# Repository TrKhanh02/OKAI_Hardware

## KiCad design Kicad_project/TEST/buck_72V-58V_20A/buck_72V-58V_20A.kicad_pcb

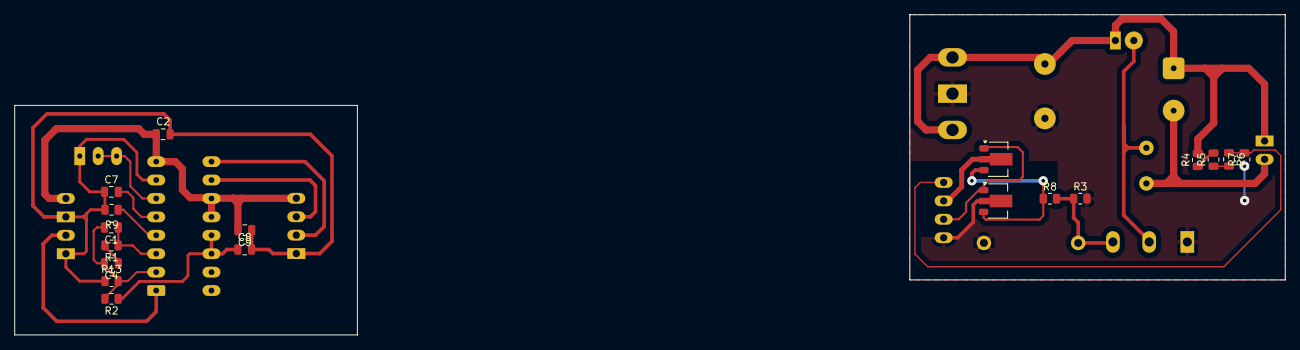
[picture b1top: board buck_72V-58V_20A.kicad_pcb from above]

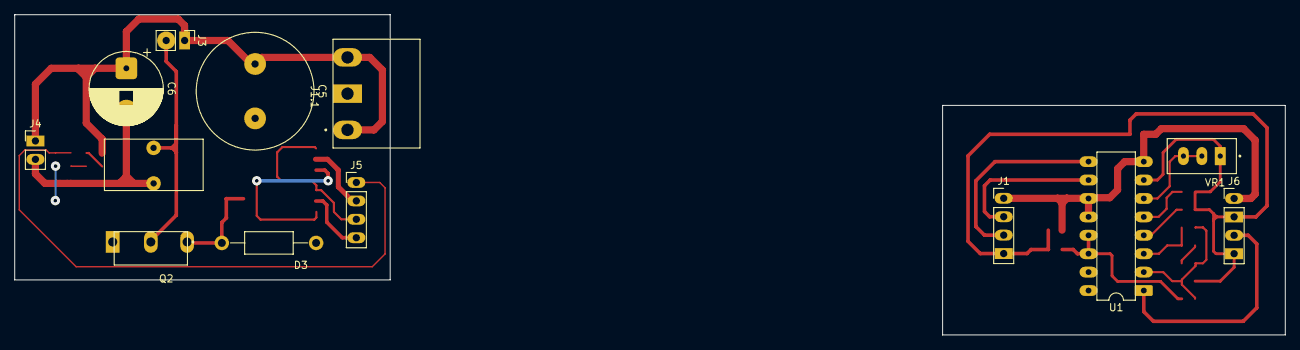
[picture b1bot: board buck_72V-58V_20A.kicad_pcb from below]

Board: 2 copper layers, 175.2 x 44.2 mm, 31 parts (13 on the bottom side), 23 nets.

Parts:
C1: 221; C_0805_2012Metric
C2, C8, C9: 104; C_0805_2012Metric
C4: 103; C_0805_2012Metric
C5: C; C_Radial_D16.0mm_H25.0mm_P7.50mm
C6: C_Polarized; CP_Radial_D10.0mm_P2.50mm
C7: 4.7nF; C_0805_2012Metric
D3: P6KE12CA; DIOAD1300W80L670D310
J1, J5, J6: Conn_01x04_Pin; PinHeader_1x04_P2.54mm_Vertical
J1.1: Nguon IN; CUI_TBP04R1-500-03BE
J3, J4: Conn_01x02_Pin; PinHeader_1x02_P2.54mm_Vertical
L1.1: FIT68-3; IND_FIT68-3
Q1: D882; TO-252
Q2: FDA50N50; TO254P1010X460X1940-3
Q3: B772
R1, R2, R3, R4, R5, R9, R13: 10K; R_0805_2012Metric
R6, R8: 1K; R_0805_2012Metric
R7: 5.6K; R_0805_2012Metric
U1: TL494; DIP-16_W7.62mm
VR1: VR1; TRIM_3296W-1-104LF

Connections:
+12V: C2.2, C9.2, J1.1, J6.1, U1.8 (C1), U1.11 (C2), U1.12 (VCC)
/16V: C5.1, C6.1, J1.1.1, J1.1.3, J3.1, J4.1
/B: C6.2, J4.2, L1.1.2, R4.2
/E: J5.3, Q1.1, Q3.1 (B)
/E1: J1.3, U1.9 (E1)
/E2: J1.2, U1.10 (E2)
/VCC: J5.2, Q1.3
/Vadj: J6.3, U1.1 (1IN+)
/Vadj1: J5.1, R6.1, R7.2
/Vref: C8.1, R2.1, U1.13 (OUTCTRL), U1.14 (REF)
GND: C2.1, C7.1, C8.2, C9.1, J1.4, J6.2, J6.4, R9.2, R13.1, U1.7 (GND), VR1.1
GND1: C5.2, D3.1, J1.1.2, J5.4, Q2.3, Q3.3 (E), R3.2, R7.1
unnamed: C4.1, R1.2
unnamed: D3.2, Q2.1, R3.1, R8.2
unnamed: J3.2, L1.1.1, Q2.2
unnamed: Q1.2, Q3.2 (C), R8.1
unnamed: R4.1, R5.2
unnamed: R5.1, R6.2
unnamed: C1.2, C4.2, R2.2, R13.2, U1.2 (1IN-)
unnamed: C7.2, U1.5 (CT)
unnamed: R9.1, U1.4 (DTC)
unnamed: C1.1, R1.1, U1.3 (FB)
unnamed: U1.6 (RT), VR1.2, VR1.3

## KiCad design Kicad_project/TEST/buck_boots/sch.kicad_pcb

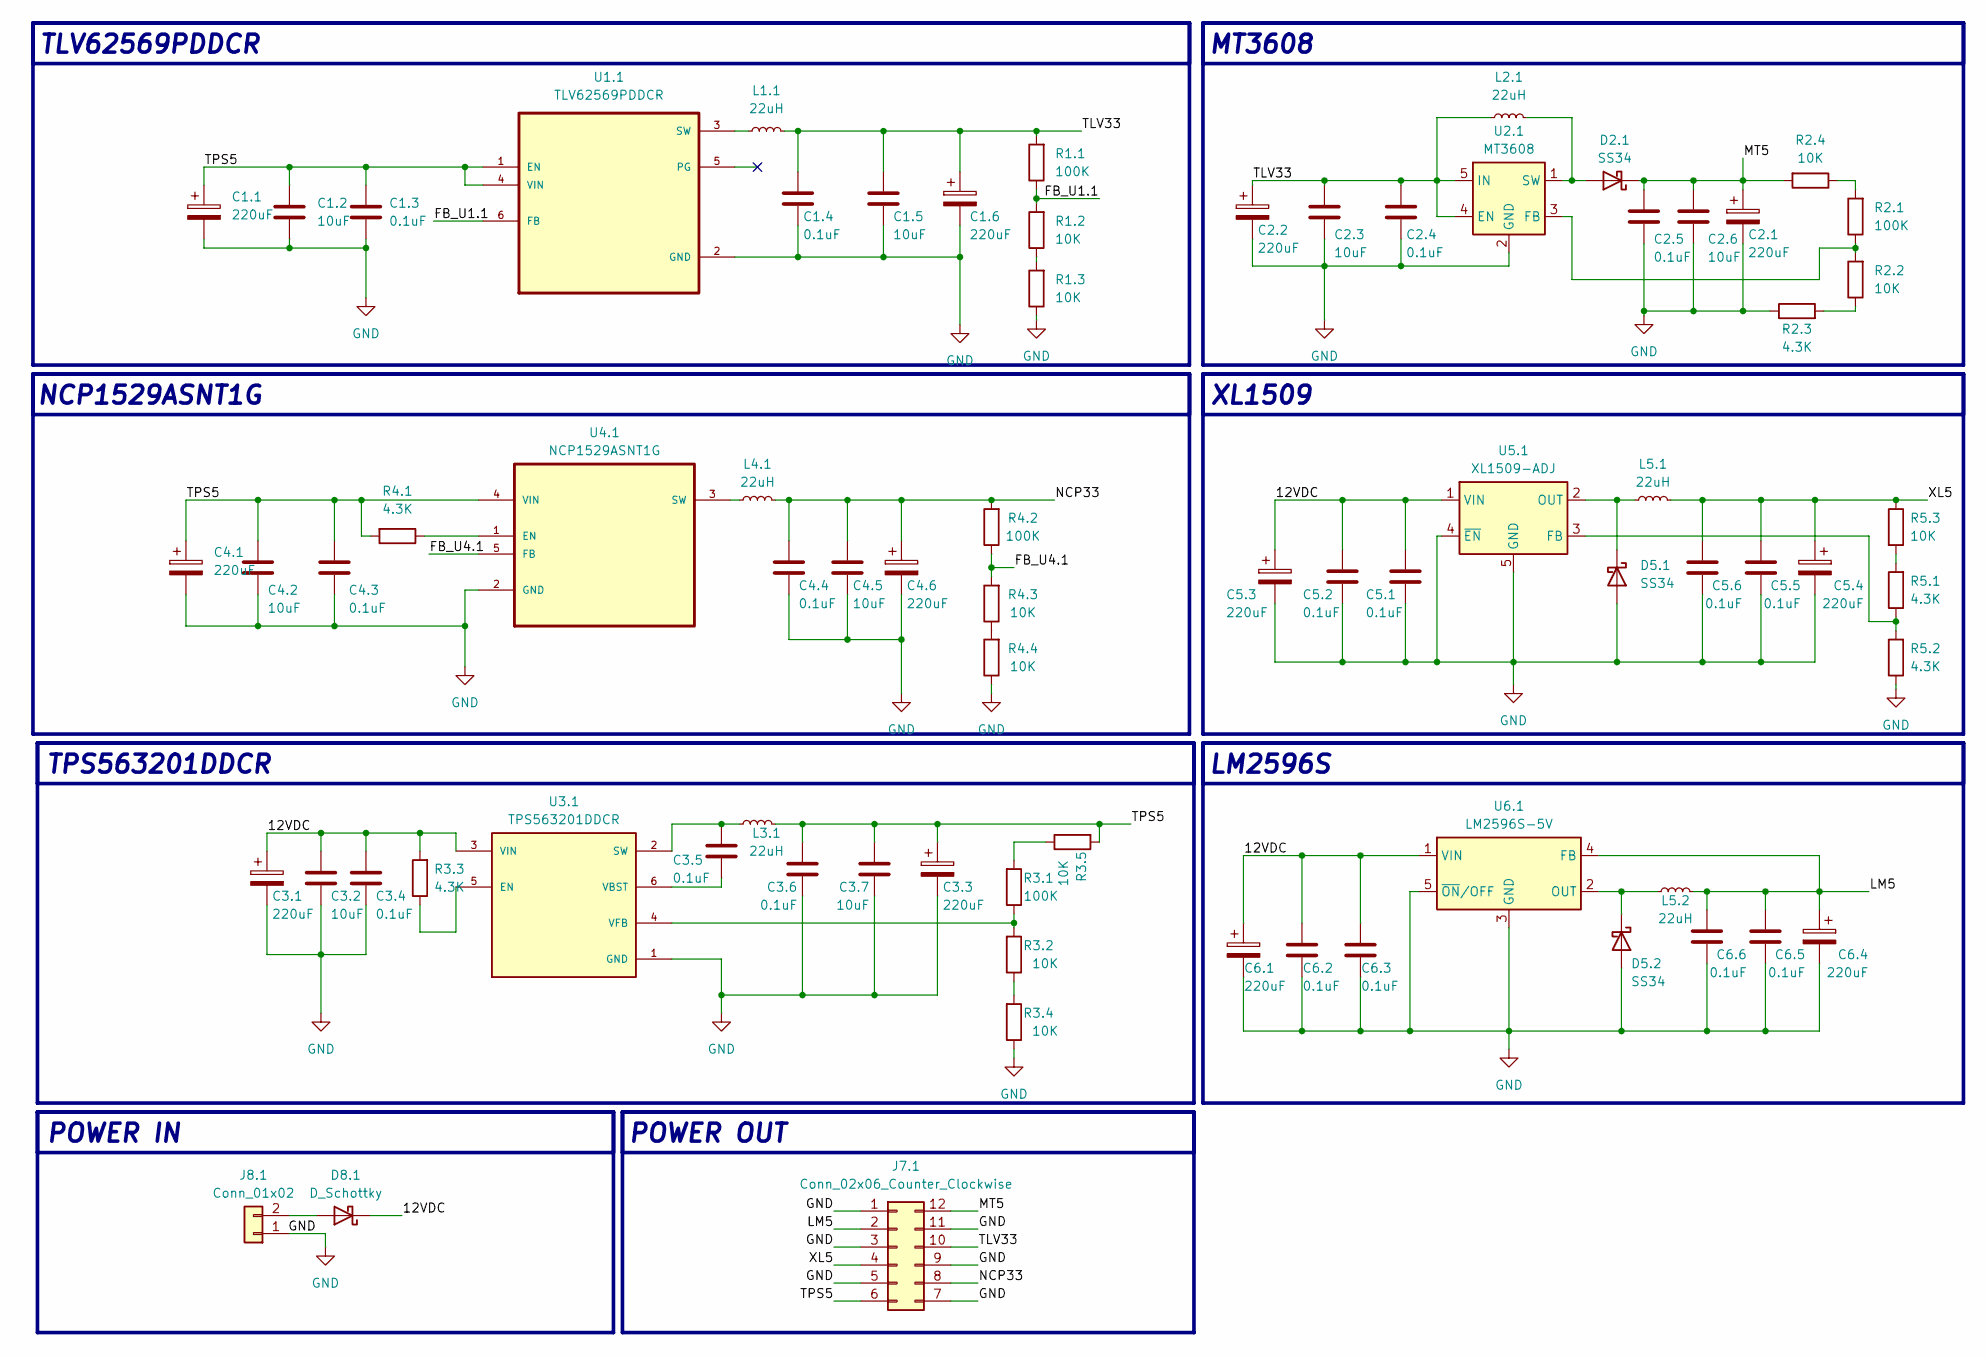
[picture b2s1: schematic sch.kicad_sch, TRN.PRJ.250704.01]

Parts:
C1.1, C1.6, C2.1, C2.2, C3.1, C3.3, C4.1, C4.6, C5.3, C5.4, C6.1, C6.4: 220uF; CP_Elec_6.3x7.7
C1.2, C1.5, C2.3, C2.6, C3.2, C3.7, C4.2, C4.5: 10uF; C_0805_2012Metric
C1.3, C1.4, C2.4, C2.5, C3.4, C3.5, C3.6, C4.3, C4.4, C5.1, C5.2, C5.5, C5.6, C6.2, C6.3, C6.5, C6.6: 0.1uF; C_0805_2012Metric
D2.1, D5.1, D5.2: SS34; D_SMA
D8.1: D_Schottky; D_SMA
J7.1: Conn_02x06_Counter_Clockwise; PinHeader_2x06_P2.54mm_Vertical
J8.1: Conn_01x02; PinSocket_1x02_P2.54mm_Vertical
L1.1, L2.1, L3.1, L4.1, L5.1, L5.2: 22uH; L_Ferrocore_DLG-0705
R1.1, R2.1, R3.1, R4.2: 100K; R_0805_2012Metric
R1.2, R1.3, R2.2, R2.4, R3.2, R3.4, R3.5, R4.3, R4.4, R5.3: 10K; R_0805_2012Metric
R2.3, R3.3, R4.1, R5.1, R5.2: 4.3K; R_0805_2012Metric
U1.1: TLV62569PDDCR; SOT95P280X110-6N
U2.1: MT3608; SOT-23-6
U3.1: TPS563201DDCR; SOT95P280X110-6N; PARTREV December 2015
U4.1: NCP1529ASNT1G; SOT95P275X110-5N
U5.1: XL1509-ADJ; SOIC-8_3.9x4.9mm_P1.27mm
U6.1: LM2596S-5V; TO-263-5_TabPin3

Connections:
/12VDC: C3.1.1, C3.2.1, C3.4.1, C5.1.1, C5.2.1, C5.3.1, C6.1.1, C6.2.1, C6.3.1, D8.1.1 (K), R3.3.2, U3.1.3 (VIN), U5.1.1 (VIN), U6.1.1 (VIN)
/FB_U1.1: R1.1.1, R1.2.2, U1.1.6 (FB)
/FB_U4.1: R4.2.1, R4.3.2, U4.1.5 (FB)
/LM5: C6.4.1, C6.5.1, C6.6.1, J7.1.2, L5.2.2, U6.1.4 (FB)
/MT5: C2.1.1, C2.5.1, C2.6.1, D2.1.1 (K), J7.1.12, R2.4.2
/NCP33: C4.4.1, C4.5.1, C4.6.1, J7.1.8, L4.1.2, R4.2.2
/TLV33: C1.4.1, C1.5.1, C1.6.1, C2.2.1, C2.3.1, C2.4.1, J7.1.10, L1.1.1, L2.1.1, R1.1.2, U2.1.4 (EN), U2.1.5 (IN)
/TPS5: C1.1.1, C1.2.1, C1.3.1, C3.3.1, C3.6.1, C3.7.1, C4.1.1, C4.2.1, C4.3.1, J7.1.6, L3.1.2, R3.5.2, R4.1.2, U1.1.1 (EN), U1.1.4 (VIN), U4.1.4 (VIN)
/XL5: C5.4.1, C5.5.1, C5.6.1, J7.1.4, L5.1.2, R5.3.1
GND: C1.1.2, C1.2.2, C1.3.2, C1.4.2, C1.5.2, C1.6.2, C2.1.2, C2.2.2, C2.3.2, C2.4.2, C2.5.2, C2.6.2, C3.1.2, C3.2.2, C3.3.2, C3.4.2, C3.6.2, C3.7.2, C4.1.2, C4.2.2, C4.3.2, C4.4.2, C4.5.2, C4.6.2, C5.1.2, C5.2.2, C5.3.2, C5.4.2, C5.5.2, C5.6.2, C6.1.2, C6.2.2, C6.3.2, C6.4.2, C6.5.2, C6.6.2, D5.1.2 (A), D5.2.2 (A), J7.1.1, J7.1.3, J7.1.5, J7.1.7, J7.1.9, J7.1.11, J8.1.1, R1.3.1, R2.3.1, R3.4.1, R4.4.1, R5.2.1, U1.1.2 (GND), U2.1.2 (GND), U3.1.1 (GND), U4.1.2 (GND), U5.1.4 (~EN), U5.1.5 (GND), U5.1.6 (GND), U5.1.7 (GND), U5.1.8 (GND), U6.1.3 (GND), U6.1.5 (~ON/OFF)
unnamed: D2.1.2 (A), L2.1.2, U2.1.1 (SW)
unnamed: D5.1.1 (K), L5.1.1, U5.1.2 (OUT)
unnamed: D5.2.1 (K), L5.2.1, U6.1.2 (OUT)
unnamed: D8.1.2 (A), J8.1.2
unnamed: R1.2.1, R1.3.2
unnamed: R2.1.2, R2.4.1
unnamed: R2.2.1, R2.3.2
unnamed: R3.1.2, R3.5.1
unnamed: R3.2.1, R3.4.2
unnamed: R4.3.1, R4.4.2
unnamed: R5.1.2, R5.3.2
unnamed: L1.1.2, U1.1.3 (SW)
unnamed: R2.1.1, R2.2.2, U2.1.3 (FB)
unnamed: R3.3.1, U3.1.5 (EN)
unnamed: C3.5.1, L3.1.1, U3.1.2 (SW)
unnamed: C3.5.2, U3.1.6 (VBST)
unnamed: R3.1.1, R3.2.2, U3.1.4 (VFB)
unnamed: R4.1.1, U4.1.1 (EN)
unnamed: L4.1.1, U4.1.3 (SW)
unnamed: R5.1.1, R5.2.2, U5.1.3 (FB)

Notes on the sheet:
LM2596S
POWER OUT
XL1509
POWER IN
TLV62569PDDCR
NCP1529ASNT1G
MT3608
TPS563201DDCR

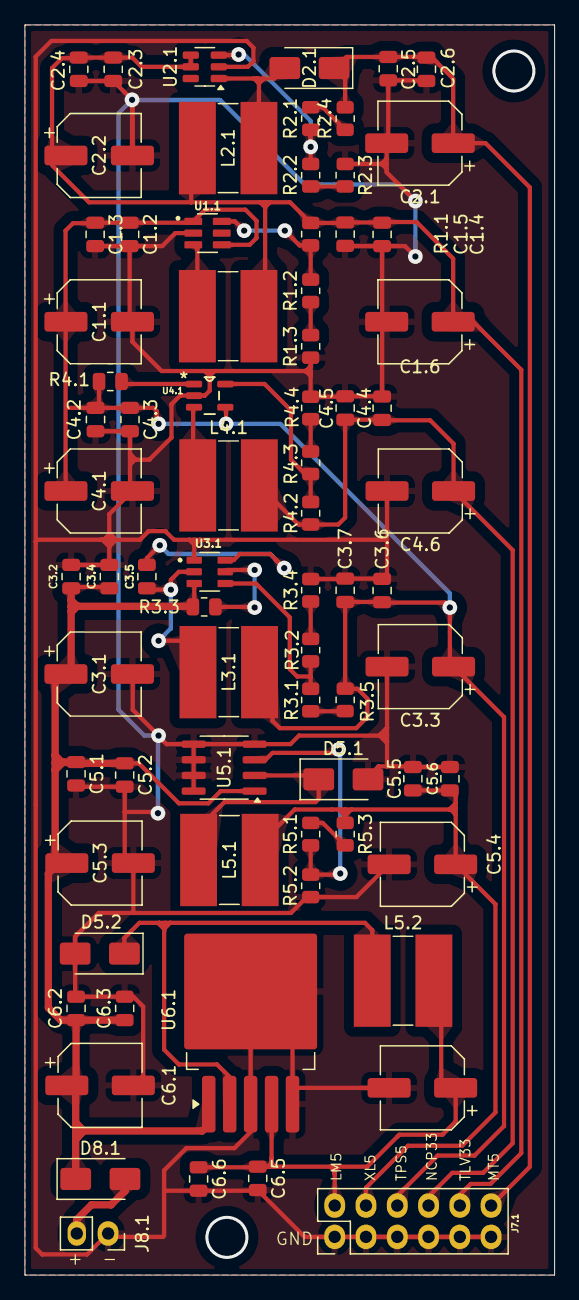
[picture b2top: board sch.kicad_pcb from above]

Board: 2 copper layers, 43.0 x 101.5 mm, 74 parts (0 on the bottom side), 30 nets.

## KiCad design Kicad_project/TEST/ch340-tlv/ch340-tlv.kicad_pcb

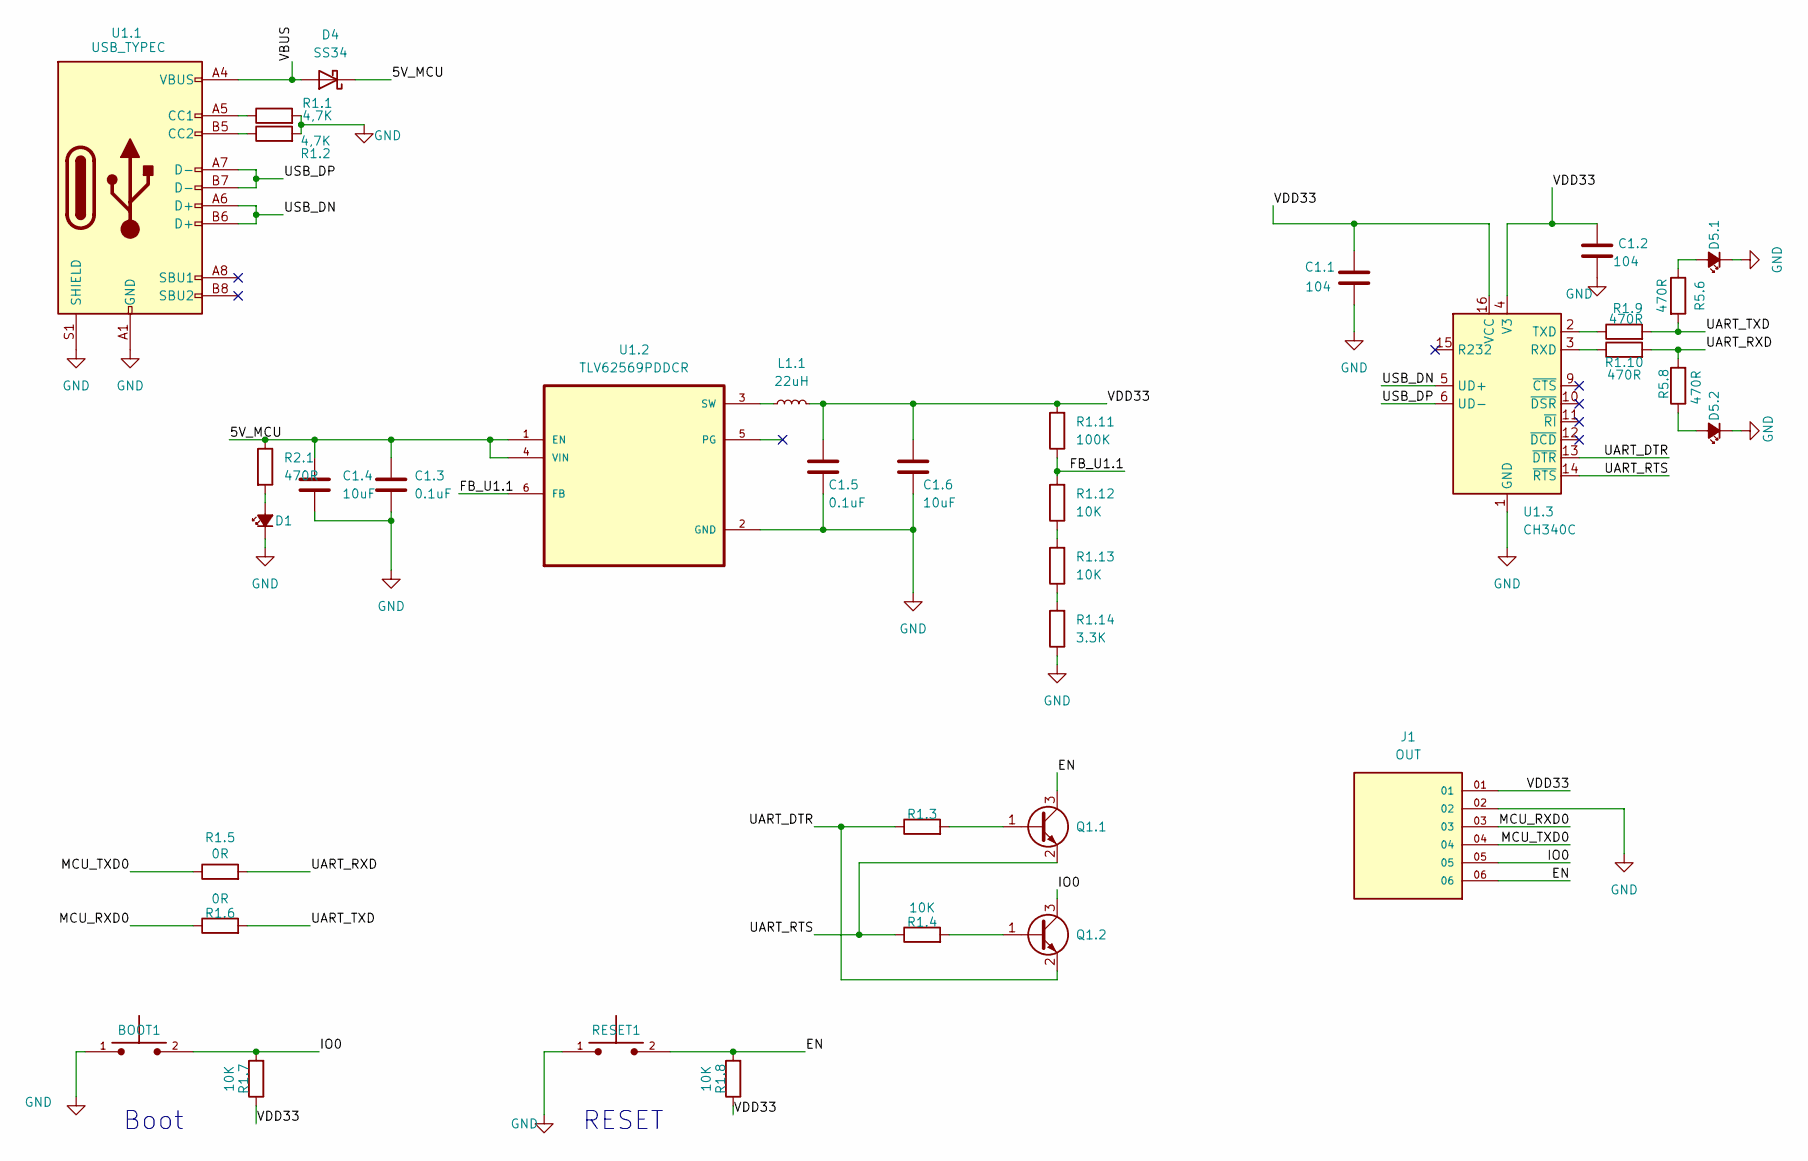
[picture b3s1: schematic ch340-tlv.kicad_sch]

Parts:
BOOT1: TS10-63-26-BE-250-SMT-TR; SW_TS10-63-26-BE-250-SMT-TR; PARTREV 1.0
C1.1, C1.2: 104; C_0805_2012Metric_Pad1.18x1.45mm_HandSolder
C1.3, C1.5: 0.1uF; C_0805_2012Metric
C1.4, C1.6: 10uF; C_0805_2012Metric
D1, D5.1, D5.2: LED_Small_Filled; LED_0805_2012Metric_Pad1.15x1.40mm_HandSolder
D4: SS34; D_SMA
J1: OUT; SAMTEC_TSW-106-08-T-S-LL; PARTREV R
L1.1: 22uH; L_Ferrocore_DLG-0705
Q1.1, Q1.2: SS8050; SOT-23
R1.1, R1.2: 4,7K; R_0805_2012Metric_Pad1.20x1.40mm_HandSolder
R1.3, R1.4, R1.7, R1.8: 10K; R_0805_2012Metric_Pad1.20x1.40mm_HandSolder
R1.5, R1.6: 0R; R_0805_2012Metric_Pad1.20x1.40mm_HandSolder
R1.9, R1.10, R2.1, R5.6, R5.8: 470R; R_0805_2012Metric_Pad1.20x1.40mm_HandSolder
R1.11: 100K; R_0805_2012Metric
R1.12, R1.13: 10K; R_0805_2012Metric
R1.14: 3.3K; R_0805_2012Metric
RESET1: TS10-63-26-BE-250-SMT-TR; SW_TS10-63-26-BE-250-SMT-TR; PARTREV 1.0
U1.1: USB_TYPEC; USB_C_Receptacle_HRO_TYPE-C-31-M-12
U1.2: TLV62569PDDCR; SOT95P280X110-6N
U1.3: CH340C; SOIC-16_3.9x9.9mm_P1.27mm

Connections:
/5V_MCU: C1.3.1, C1.4.1, D4.1 (K), R2.1.1, U1.2.1 (EN), U1.2.4 (VIN)
/EN: J1.06, Q1.1.3 (C), R1.8.2, RESET1.2
/FB_U1.1: R1.11.1, R1.12.2, U1.2.6 (FB)
/IO0: BOOT1.2, J1.05, Q1.2.3 (C), R1.7.2
/MCU_RXD0: J1.03, R1.6.1
/MCU_TXD0: J1.04, R1.5.1
/UART_DTR: Q1.2.2 (E), R1.3.1, U1.3.13 (~DTR)
/UART_RTS: Q1.1.2 (E), R1.4.1, U1.3.14 (~RTS)
/UART_RXD: R1.5.2, R1.10.2, R5.8.2
/UART_TXD: R1.6.2, R1.9.2, R5.6.2
/USB_DN: U1.1.A6 (D+), U1.1.B6 (D+), U1.3.5 (UD+)
/USB_DP: U1.1.A7 (D-), U1.1.B7 (D-), U1.3.6 (UD-)
/VBUS: D4.2 (A), U1.1.A4 (VBUS), U1.1.A9 (VBUS), U1.1.B4 (VBUS), U1.1.B9 (VBUS)
/VDD33: C1.1.2, C1.2.2, C1.5.1, C1.6.1, J1.01, L1.1.1, R1.7.1, R1.8.1, R1.11.2, U1.3.4 (V3), U1.3.16 (VCC)
GND: BOOT1.1, C1.1.1, C1.2.1, C1.3.2, C1.4.2, C1.5.2, C1.6.2, D1.1 (K), D5.1.1 (K), D5.2.1 (K), J1.02, R1.1.2, R1.2.2, R1.14.1, RESET1.1, U1.1.A1 (GND), U1.1.A12 (GND), U1.1.B1 (GND), U1.1.B12 (GND), U1.1.S1 (SHIELD), U1.2.2 (GND), U1.3.1 (GND)
unnamed: D1.2 (A), R2.1.2
unnamed: D5.1.2 (A), R5.6.1
unnamed: D5.2.2 (A), R5.8.1
unnamed: Q1.1.1 (B), R1.3.2
unnamed: Q1.2.1 (B), R1.4.2
unnamed: R1.12.1, R1.13.2
unnamed: R1.13.1, R1.14.2
unnamed: R1.1.1, U1.1.A5 (CC1)
unnamed: R1.2.1, U1.1.B5 (CC2)
unnamed: L1.1.2, U1.2.3 (SW)
unnamed: R1.10.1, U1.3.3 (RXD)
unnamed: R1.9.1, U1.3.2 (TXD)

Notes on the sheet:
RESET
Boot

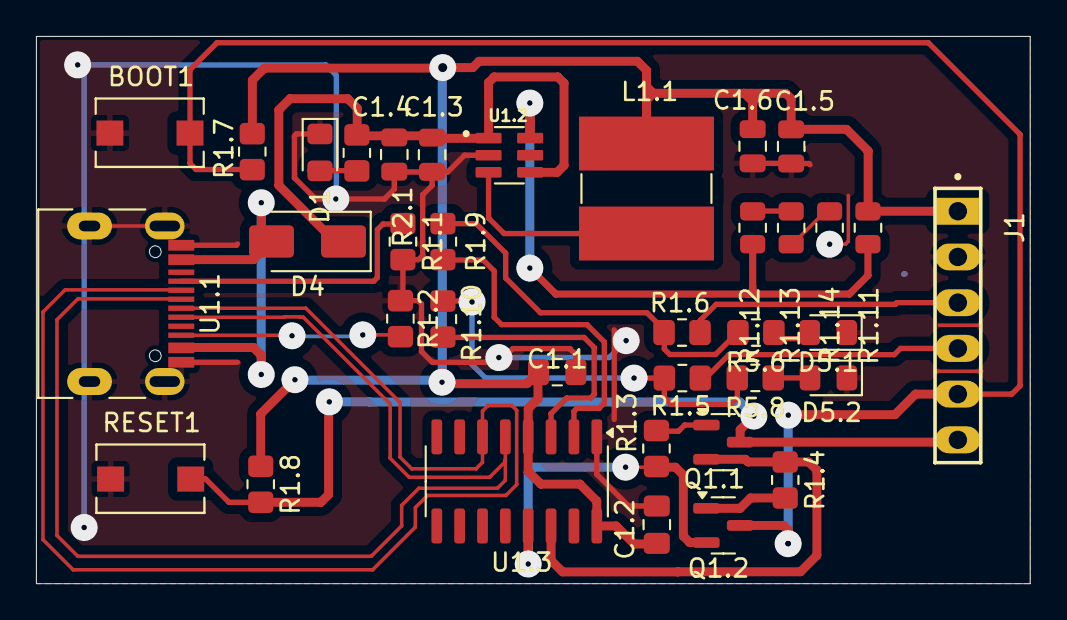
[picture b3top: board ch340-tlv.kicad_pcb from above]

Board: 2 copper layers, 55.2 x 30.4 mm, 36 parts (0 on the bottom side), 27 nets.

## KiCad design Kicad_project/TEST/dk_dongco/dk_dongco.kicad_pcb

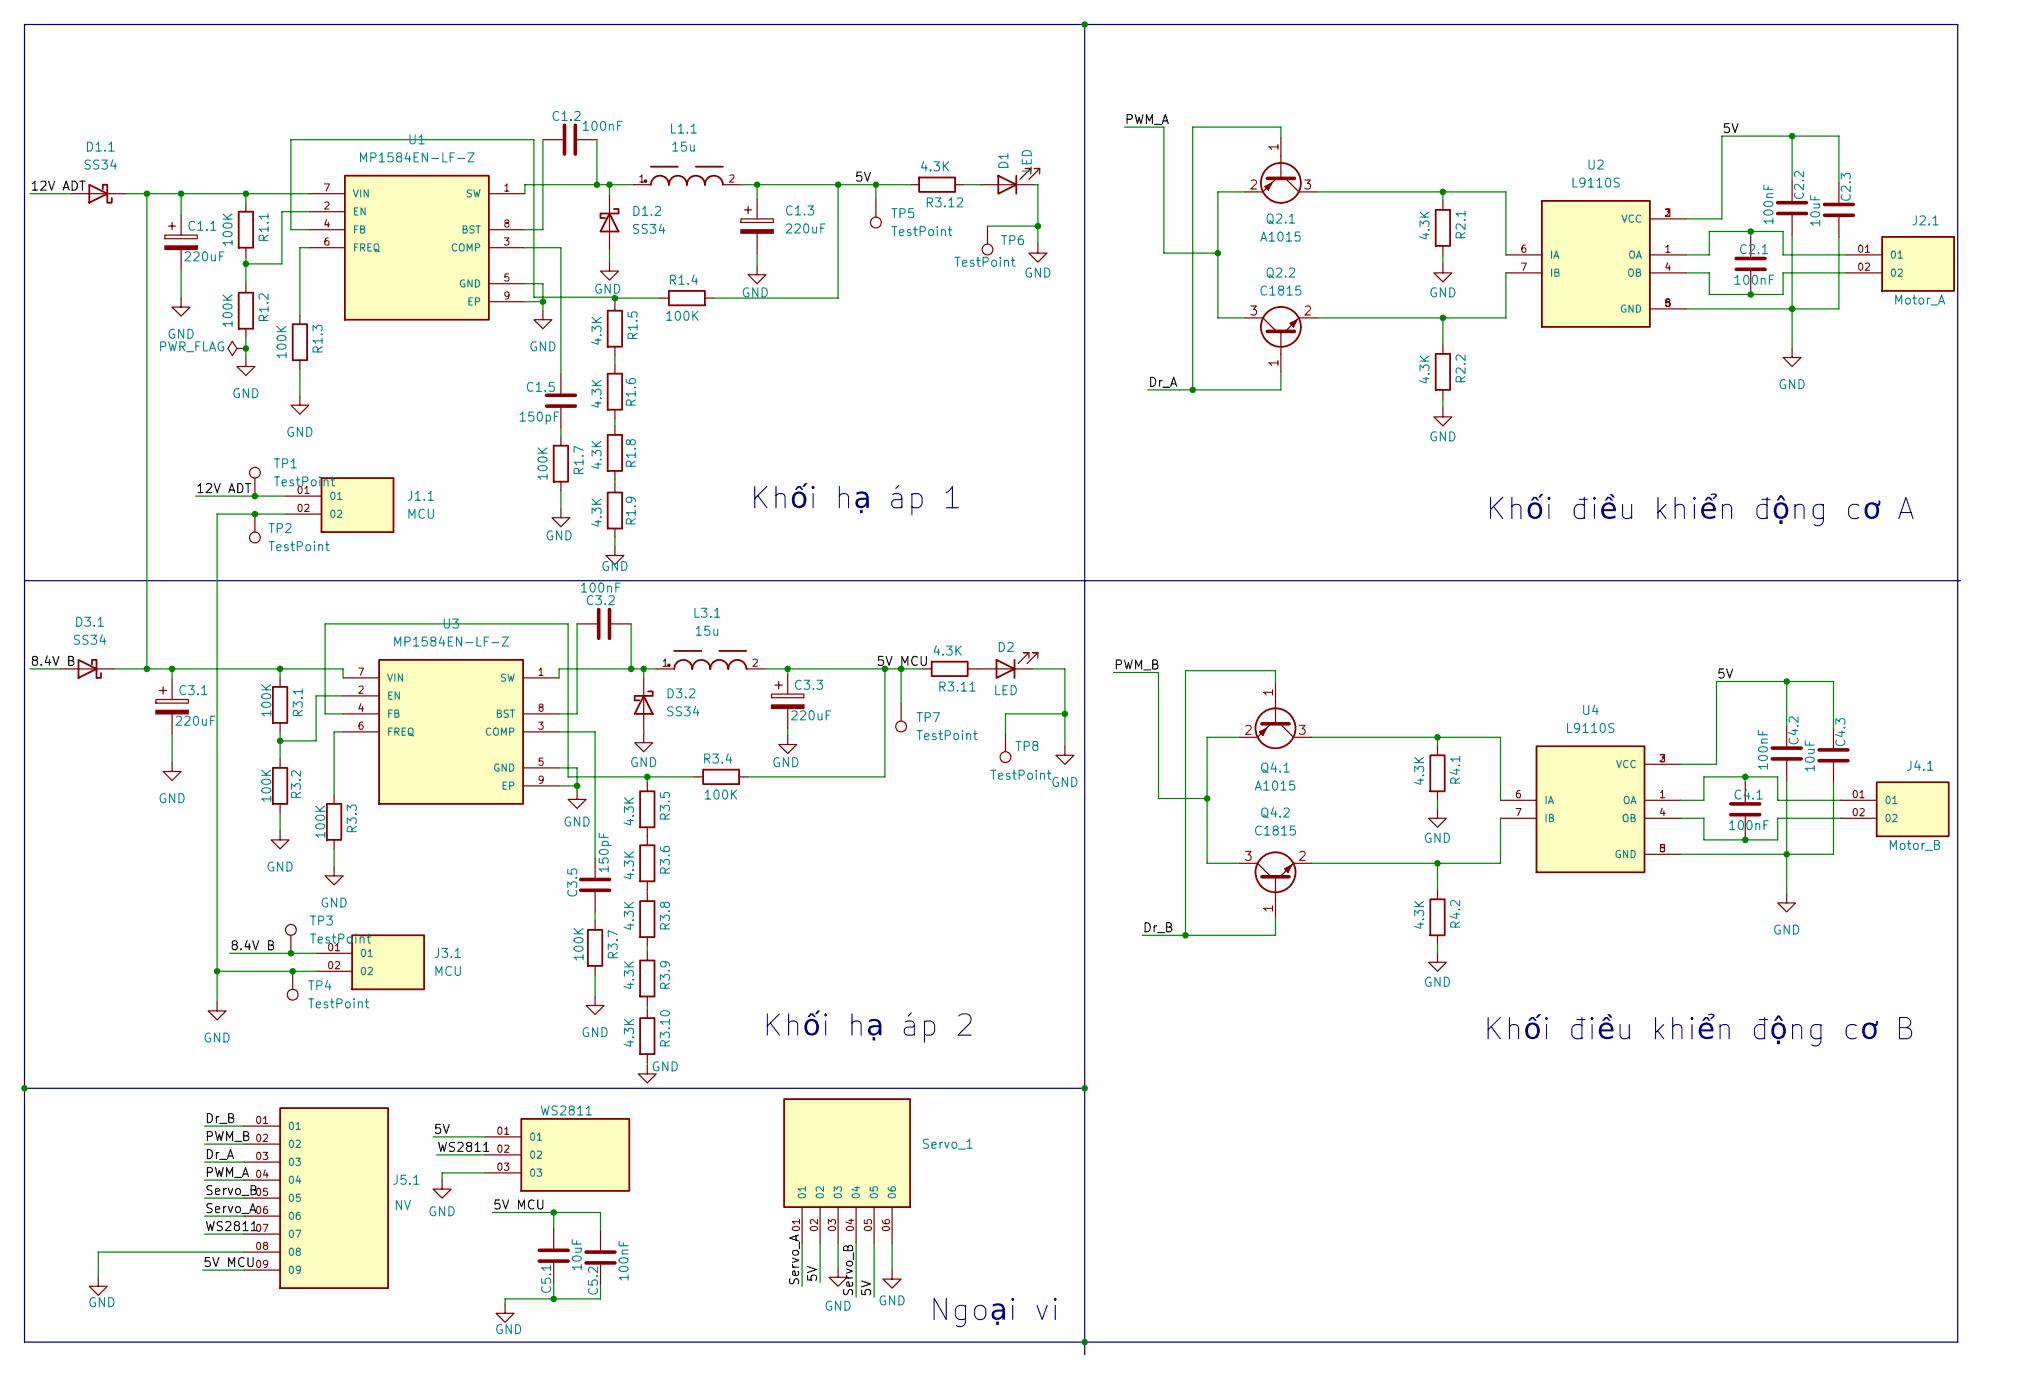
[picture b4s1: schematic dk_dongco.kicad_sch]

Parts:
C1.1, C1.3, C3.1, C3.3: 220uF; CP_Elec_6.3x7.7
C1.2, C2.1, C2.2, C3.2, C4.1, C4.2, C5.2: 100nF; C_0805_2012Metric
C1.5, C3.5: 150pF; C_0805_2012Metric
C2.3, C4.3, C5.1: 10uF; C_0805_2012Metric
D1, D2: LED; LED_0805_2012Metric_Pad1.15x1.40mm_HandSolder
D1.1, D1.2, D3.1, D3.2: SS34; D_1210_3225Metric_Pad1.42x2.65mm_HandSolder
J1.1, J3.1: MCU; SAMTEC_HTSW-102-08-TM-S
J2.1: Motor_A; SAMTEC_HTSW-102-08-TM-S
J4.1: Motor_B; SAMTEC_HTSW-102-08-TM-S
J5.1: NV; SAMTEC_TSW-109-14-G-S; PARTREV R
L1.1, L3.1: 15u; WE-PD_7332R
Q2.1, Q4.1: A1015; SOT-23
Q2.2, Q4.2: C1815; SOT-23
R1.1, R1.2, R1.3, R1.4, R1.7, R3.1, R3.2, R3.3, R3.4, R3.7: 100K; R_0805_2012Metric_Pad1.20x1.40mm_HandSolder
R1.5, R1.6, R1.8, R1.9, R2.1, R2.2, R3.5, R3.6, R3.8, R3.9, R3.10, R3.11, R3.12, R4.1, R4.2: 4.3K; R_0805_2012Metric_Pad1.20x1.40mm_HandSolder
Servo_1: MTSW-106-08-T-S-310; SAMTEC_MTSW-106-08-T-S-310; PARTREV R
TP1, TP2, TP3, TP4, TP5, TP6, TP7, TP8: TestPoint; TestPoint_Pad_1.0x1.0mm
U1, U3: MP1584EN-LF-Z; SOIC127P600X170-9N
U2, U4: L9110S; SOIC127P599X172-8N; PARTREV NA
WS2811: MTSW-a103-10-S-S-580; SAMTEC_MTSW-103-10-S-S-580; PARTREV R

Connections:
/5V: C1.3.1, C2.2.1, C2.3.1, C4.2.1, C4.3.1, L1.1.2, R1.4.2, R3.12.2, Servo_1.02, Servo_1.05, TP5.1, U2.2 (VCC), U2.3 (VCC), U4.2 (VCC), U4.3 (VCC), WS2811.01
/5V MCU: C3.3.1, C5.1.2, C5.2.2, J5.1.09, L3.1.2, R3.4.2, R3.11.2, TP7.1
/8.4V B: D3.1.2 (A), J3.1.01, TP3.1
/12V ADT: D1.1.2 (A), J1.1.01, TP1.1
/Dr_A: J5.1.03, Q2.1.1 (B), Q2.2.1 (B)
/Dr_B: J5.1.01, Q4.1.1 (B), Q4.2.1 (B)
/PWM_A: J5.1.04, Q2.1.2 (E), Q2.2.3 (C)
/PWM_B: J5.1.02, Q4.1.2 (E), Q4.2.3 (C)
/Servo_A: J5.1.06, Servo_1.01
/Servo_B: J5.1.05, Servo_1.04
/WS2811: J5.1.07, WS2811.02
GND: C1.1.2, C1.3.2, C2.2.2, C2.3.2, C3.1.2, C3.3.2, C4.2.2, C4.3.2, C5.1.1, C5.2.1, D1.1 (K), D1.2.2 (A), D2.1 (K), D3.2.2 (A), J1.1.02, J3.1.02, J5.1.08, R1.2.2, R1.3.2, R1.7.2, R1.9.2, R2.1.2, R2.2.2, R3.2.2, R3.3.2, R3.7.2, R3.10.2, R4.1.2, R4.2.2, Servo_1.03, Servo_1.06, TP2.1, TP4.1, TP6.1, TP8.1, U1.5 (GND), U1.9 (EP), U2.5 (GND), U2.8 (GND), U3.5 (GND), U3.9 (EP), U4.5 (GND), U4.8 (GND), WS2811.03
unnamed: C1.5.2, R1.7.1
unnamed: C3.5.2, R3.7.1
unnamed: D1.2 (A), R3.12.1
unnamed: C1.1.1, C3.1.1, D1.1.1 (K), D3.1.1 (K), R1.1.1, R3.1.1, U1.7 (VIN), U3.7 (VIN)
unnamed: C1.2.2, D1.2.1 (K), L1.1.1, U1.1 (SW)
unnamed: D2.2 (A), R3.11.1
unnamed: C3.2.2, D3.2.1 (K), L3.1.1, U3.1 (SW)
unnamed: Q2.1.3 (C), R2.1.1, U2.6 (IA)
unnamed: Q2.2.2 (E), R2.2.1, U2.7 (IB)
unnamed: Q4.1.3 (C), R4.1.1, U4.6 (IA)
unnamed: Q4.2.2 (E), R4.2.1, U4.7 (IB)
unnamed: R1.5.2, R1.6.1
unnamed: R1.6.2, R1.8.1
unnamed: R1.8.2, R1.9.1
unnamed: R3.5.2, R3.6.1
unnamed: R3.6.2, R3.8.1
unnamed: R3.8.2, R3.9.1
unnamed: R3.9.2, R3.10.1
unnamed: C1.2.1, U1.8 (BST)
unnamed: C1.5.1, U1.3 (COMP)
unnamed: R1.1.2, R1.2.1, U1.2 (EN)
unnamed: R1.4.1, R1.5.1, U1.4 (FB)
unnamed: R1.3.1, U1.6 (FREQ)
unnamed: C2.1.1, J2.1.01, U2.1 (OA)
unnamed: C2.1.2, J2.1.02, U2.4 (OB)
unnamed: C3.2.1, U3.8 (BST)
unnamed: C3.5.1, U3.3 (COMP)
unnamed: R3.1.2, R3.2.1, U3.2 (EN)
unnamed: R3.4.1, R3.5.1, U3.4 (FB)
unnamed: R3.3.1, U3.6 (FREQ)
unnamed: C4.1.1, J4.1.01, U4.1 (OA)
unnamed: C4.1.2, J4.1.02, U4.4 (OB)

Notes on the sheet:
Khối điều khiển động cơ B
Khối hạ áp 1
Khối hạ áp 2
Ngoại vi
Khối điều khiển động cơ A

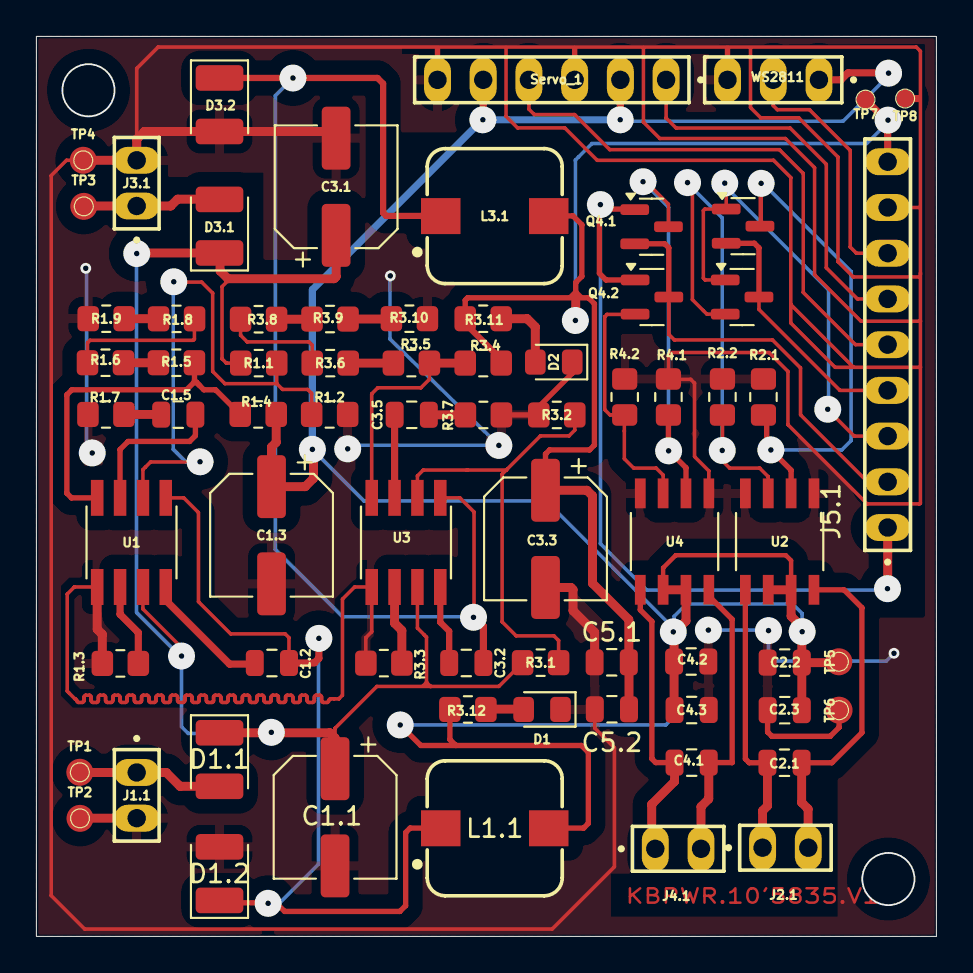
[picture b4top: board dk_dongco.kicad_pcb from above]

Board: 2 copper layers, 50.0 x 50.0 mm, 72 parts (0 on the bottom side), 44 nets.

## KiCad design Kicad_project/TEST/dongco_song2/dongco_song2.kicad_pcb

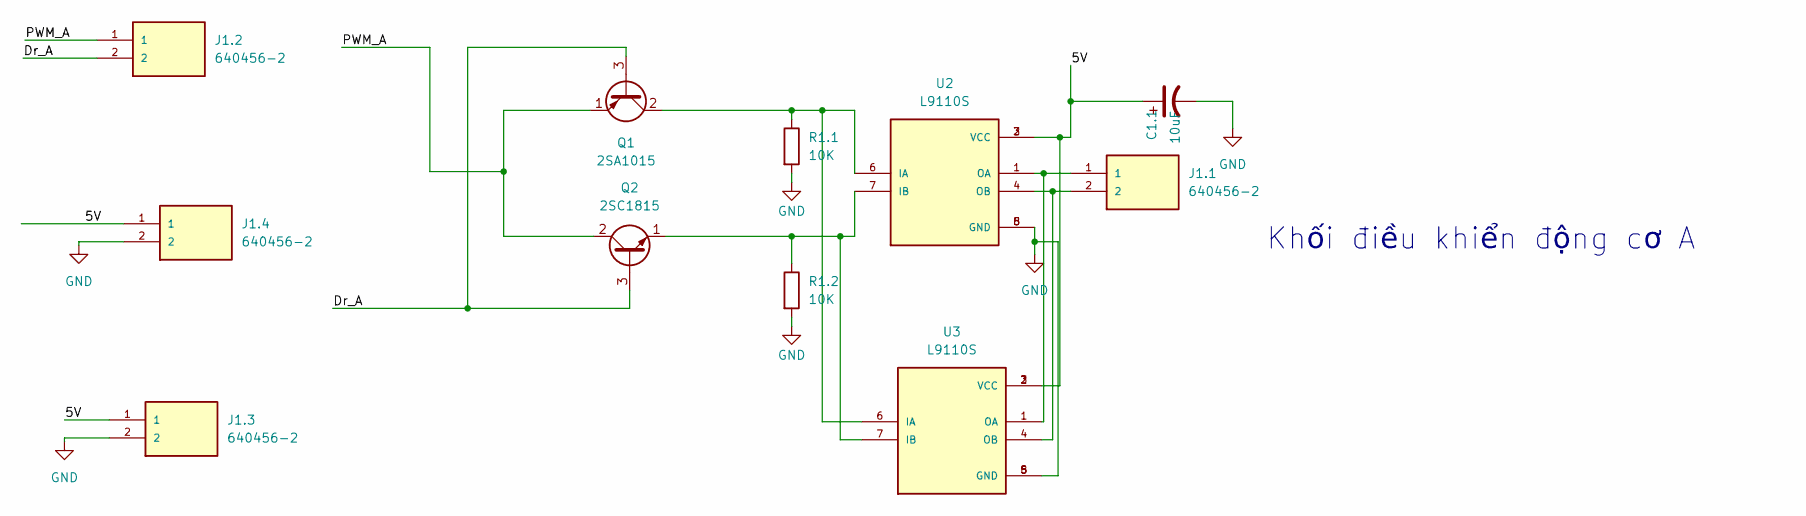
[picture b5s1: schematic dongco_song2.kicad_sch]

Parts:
C1.1: 10uF; CP_Radial_D4.0mm_P1.50mm
J1.1, J1.2, J1.3, J1.4: 640456-2; TE_640456-2; PARTREV R
Q1: 2SA1015; TO-92_Inline
Q2: 2SC1815; TO-92_Inline
R1.1, R1.2: 10K; R_Axial_DIN0207_L6.3mm_D2.5mm_P7.62mm_Horizontal
U2, U3: L9110S; SOIC127P599X172-8N; PARTREV NA

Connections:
/5V: C1.1.1, J1.3.1, J1.4.1, U2.2 (VCC), U2.3 (VCC), U3.2 (VCC), U3.3 (VCC)
/Dr_A: J1.2.2, Q1.3 (B), Q2.3 (B)
/PWM_A: J1.2.1, Q1.1 (E), Q2.2 (C)
GND: C1.1.2, J1.3.2, J1.4.2, R1.1.2, R1.2.2, U2.5 (GND), U2.8 (GND), U3.5 (GND), U3.8 (GND)
unnamed: Q1.2 (C), R1.1.1, U2.6 (IA), U3.6 (IA)
unnamed: Q2.1 (E), R1.2.1, U2.7 (IB), U3.7 (IB)
unnamed: J1.1.1, U2.1 (OA), U3.1 (OA)
unnamed: J1.1.2, U2.4 (OB), U3.4 (OB)

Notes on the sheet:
Khối điều khiển động cơ A

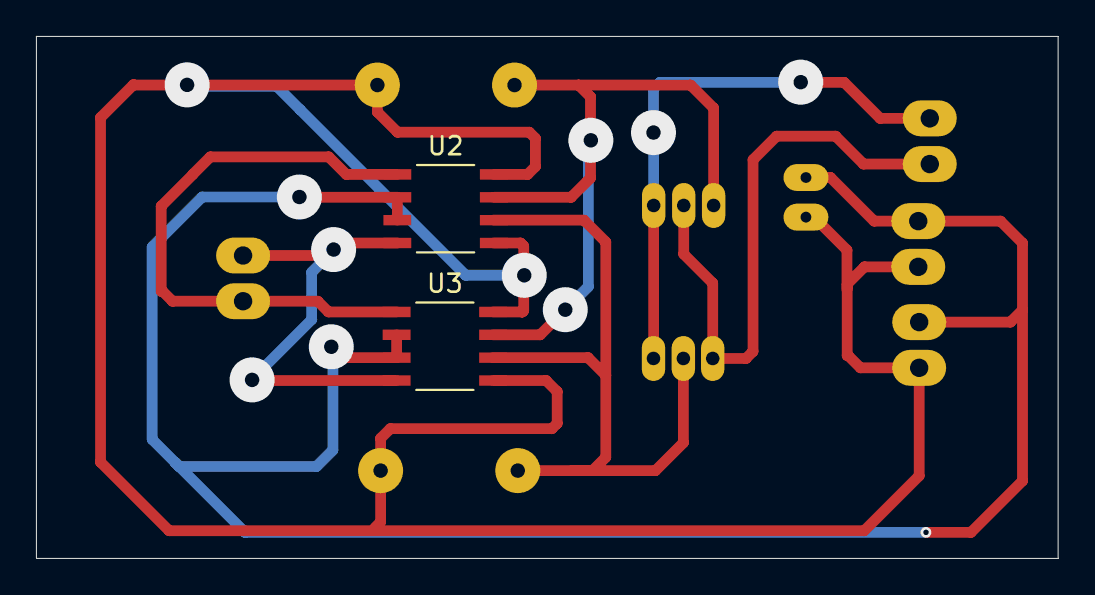
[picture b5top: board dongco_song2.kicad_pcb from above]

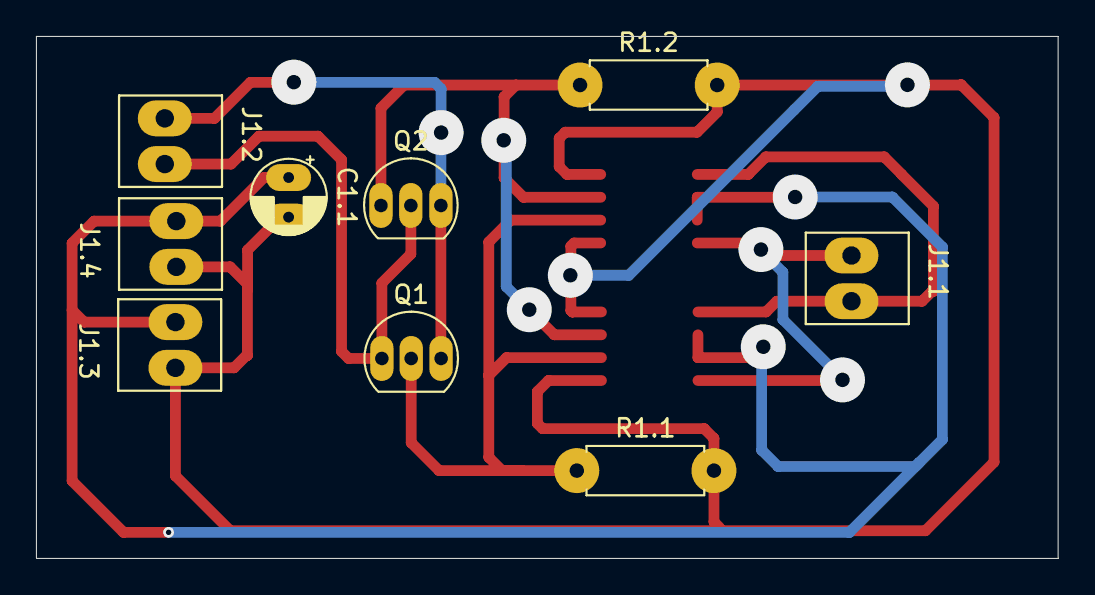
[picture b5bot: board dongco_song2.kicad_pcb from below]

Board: 2 copper layers, 56.8 x 29.0 mm, 11 parts (9 on the bottom side), 8 nets.
